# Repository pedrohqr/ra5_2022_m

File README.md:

# RA5 2022 M — Base Board (Raptor)

Base/carrier board for a modular PLC (Programmable Logic Controller): an I/O
front-end with no main MCU of its own — sensing and metering peripherals are
driven by a separate MCU+LTE modem card that plugs into the onboard M.2
Key-E socket (`J1`, visible in the photos below). The socket follows the M.2
mechanical form factor but uses a custom pinout (native 3.3V logic) — it is
not meant to accept an off-the-shelf M.2 card. The pluggable MCU+modem card
itself now lives in its own separate repository, developed independently
from this base board.

Main blocks on this board:

- **Power**: input via the `B0303S-1W` isolated DC-DC module, `TPS54202DDC`
  buck regulator, `AMS1117-3.3` linear regulator (USB rail), and a USB-C
  connector that passes through to `J1` for flashing/debugging the plugged-in
  MCU card.
- **2x differential 4-20mA analog inputs** via an `ADS1115` I2C ADC.
- **2x digital inputs and 2x digital outputs**, opto/divider-conditioned and
  transistor-driven respectively.
- **`ATM90E32AS` three-phase energy meter**, in a galvanically isolated
  domain (`GND2`/`VDD2`) from the rest of the board, bridged via the
  `ISO7741N1-Y` digital isolator (SPI) and a `CS817X20LS`-family isolator
  (power-mode select).
- **`STM8S003F3P` housekeeping MCU**, reading/driving the digital I/O signals
  and intended to expose them over the shared I2C bus on `J1`.
- `KF250-3.5-2P-2` screw terminals for the current loops and other
  field-side connections.

## Renders of the finished board

*Component-side view: the M.2 socket (`J1`) in the center, screw terminals
and field connectors along the edges, and the row of MOVs/varistors feeding
the energy-meter current inputs.*

*Same side, rotated ~180°, showing the USB-C connector, the STM8
housekeeping MCU, and the power section.*

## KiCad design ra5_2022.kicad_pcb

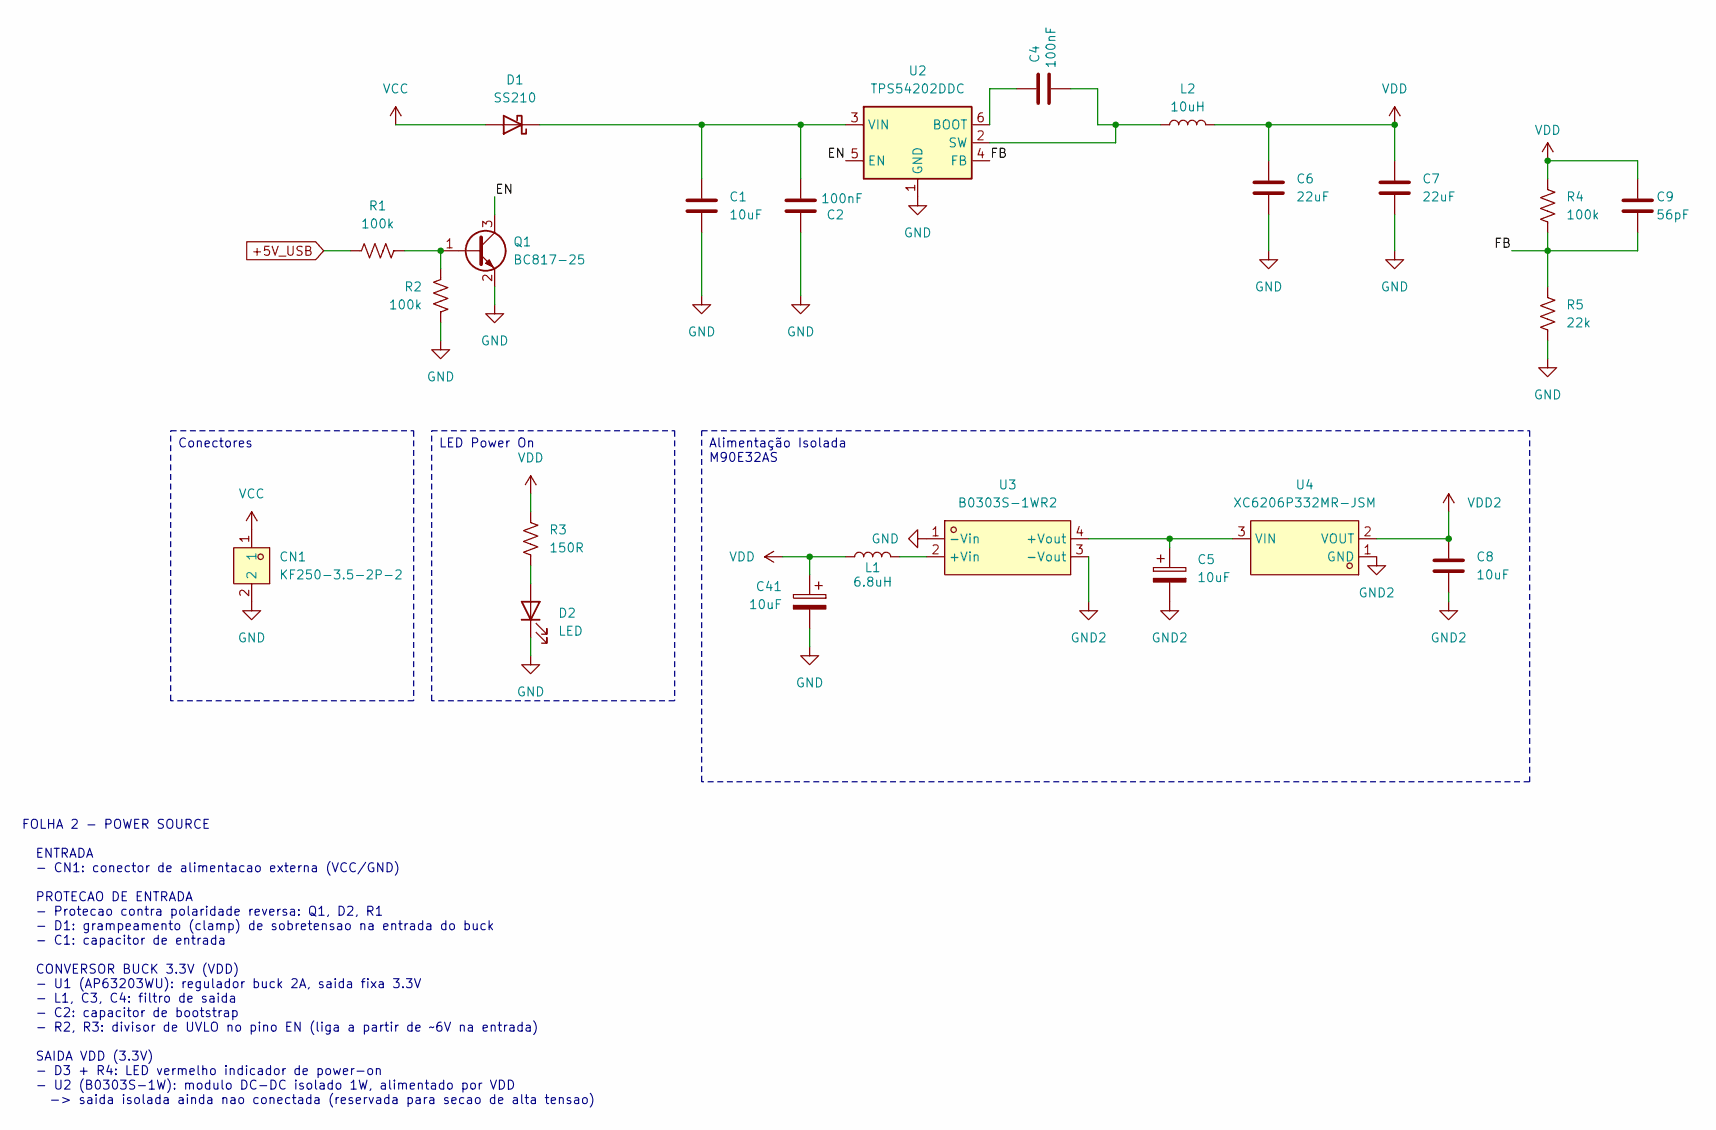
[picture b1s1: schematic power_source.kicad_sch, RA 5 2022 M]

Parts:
C1: 10uF; C_1206_3216Metric; MPN CL31A106KBHNNNE; JLCPCB Part # C13585
C2: 100nF; C_0402_1005Metric; MPN CL05B104KB54PNC; JLCPCB Part # C307331
C4: 100nF; C_0402_1005Metric; MPN CL05B104KO5NNNC; JLCPCB Part # C1525
C5, C41: 10uF; CP_Elec_4x5.4; MPN VT1E100M0405; JLCPCB Part # C22383768
C6, C7: 22uF; C_0603_1608Metric; MPN CL10A226MQ8NRNC; JLCPCB Part # C59461
C8: 10uF; C_0402_1005Metric; MPN CL05A106MQ5NUNC; JLCPCB Part # C15525
C9: 56pF; C_0603_1608Metric; MPN CL10C560JB8NNNC; JLCPCB Part # C39148
CN1: KF250-3.5-2P-2; CONN-TH_P3.50_KF250-3.5-2P-2; MPN KF250-3.5-2P-2; JLCPCB Part # C475163
D1: SS210; D_SMA; MPN SS210; JLCPCB Part # C14996
D2: LED; LED_0805_2012Metric; MPN YLED0805R; JLCPCB Part # C19171391
L1: 6.8uH; L_1008_2520Metric; MPN SLW252010S6R8MST; JLCPCB Part # C48533097
L2: 10uH; IND-SMD_L5.0-W5.0-1; MPN SLW5040S100MST; JLCPCB Part # C182189
Q1: BC817-25; SOT-23; MPN BC817-25; JLCPCB Part # C20069154
R1, R2, R4: 100k; R_0805_2012Metric; MPN 0805W8F1003T5E; JLCPCB Part # C149504
R3: 150R; R_0603_1608Metric; MPN 0603WAF1500T5E; JLCPCB Part # C22808
R5: 22k; R_0402_1005Metric; MPN 0402WGF2202TCE; JLCPCB Part # C25768
U2: TPS54202DDC; SOT-23-6; MPN TPS54202DDCR; JLCPCB Part # C191884
U3: B0303S-1WR2; PWRM-TH_BXXXXS-1WR2; MPN B0303S-1WR2; JLCPCB Part # C7598619
U4: XC6206P332MR-JSM; SOT-23-3_L3.0-W1.7-P0.95-LS2.9-BR; MPN XC6206P332MR-JSM; JLCPCB Part # C20616640

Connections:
+5V_USB: R1.1; also elsewhere on the board
/Power Source/EN: Q1.3 (C), U2.5 (EN)
/Power Source/FB: C9.2, R4.1, R5.1, U2.4 (FB)
GND: C1.2, C2.1, C6.2, C7.2, C41.2, CN1.2, D2.1 (K), Q1.2 (E), R2.1, R5.2, U2.1 (GND), U3.1 (-Vin); also elsewhere on the board
GND2: C5.2, C8.2, U3.3 (-Vout), U4.1 (GND); also elsewhere on the board
unnamed: C1.1, C2.2, D1.1 (K), U2.3 (VIN)
unnamed: D2.2 (A), R3.2
unnamed: Q1.1 (B), R1.2, R2.2
unnamed: C4.1, U2.6 (BOOT)
unnamed: C4.2, L2.1, U2.2 (SW)
unnamed: L1.2, U3.2 (+Vin)
unnamed: C5.1, U3.4 (+Vout), U4.3 (VIN)
VCC: CN1.1, D1.2 (A)
VDD: C6.1, C7.1, C9.1, C41.1, L1.1, L2.2, R3.1, R4.2; also elsewhere on the board
VDD2: C8.1, U4.2 (VOUT); also elsewhere on the board

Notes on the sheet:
FOLHA 2 - POWER SOURCE ENTRADA - CN1: conector de alimentacao externa (VCC/GND) PROTECAO DE ENTRADA - Protecao contra polaridade reversa: Q1, D2, R1 - D1: grampeamento (clamp) de sobretensao na entrada do buck - C1: capacitor de entrada CONVERSOR BUCK 3.3V (VDD) - U1 (AP63203WU): regulador buck 2A,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
Conectores
Alimentação Isolada M90E32AS
LED Power On

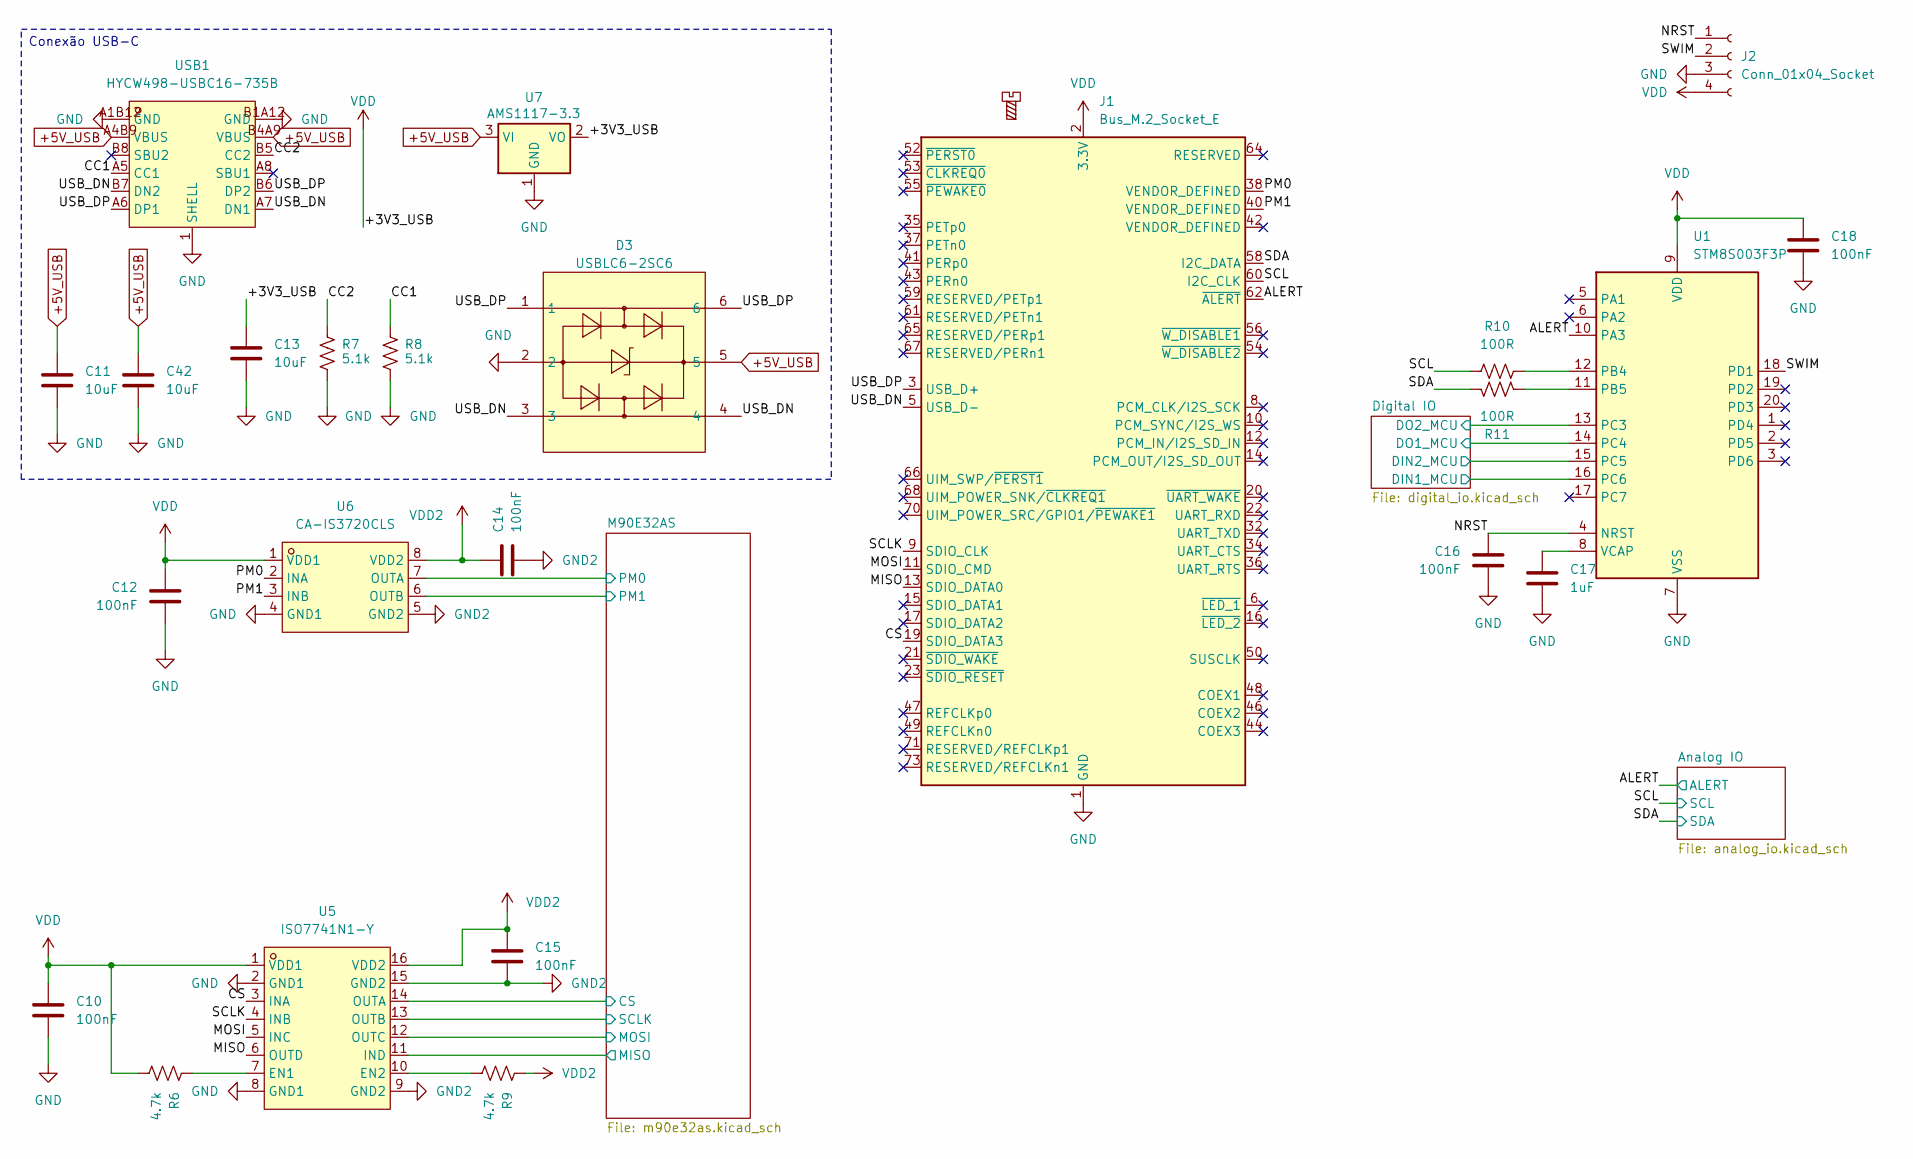
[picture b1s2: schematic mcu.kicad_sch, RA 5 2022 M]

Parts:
C10, C12, C14, C15, C16, C18: 100nF; C_0402_1005Metric; MPN CL05B104KO5NNNC; JLCPCB Part # C1525
C11, C13, C42: 10uF; C_0402_1005Metric; MPN CL05A106MQ5NUNC; JLCPCB Part # C15525
C17: 1uF; C_0402_1005Metric; MPN CL05A105KA5NQNC; JLCPCB Part # C52923
D3: USBLC6-2SC6; SOT-23-6_L2.9-W1.6-P0.95-LS2.8-BL; MPN USBLC6-2SC6; JLCPCB Part # C7519
H1: MountingScrew; MountingHole_2.2mm_M2_Pad_Via
J1: Bus_M.2_Socket_E; CONN-SMD_AS0BC21-S48BE-7H; MPN AS0BC21-S40BE-7H; JLCPCB Part # C410527
J2: Conn_01x04_Socket; PinHeader_1x04_P2.54mm_Vertical
R6, R9: 4.7k; R_0402_1005Metric; MPN 0402WGF4701TCE; JLCPCB Part # C25900
R7, R8: 5.1k; R_0603_1608Metric; MPN WR04X512JTL; JLCPCB Part # C384321
R10, R11: 100R; R_0402_1005Metric; MPN 0402WGF1000TCE; JLCPCB Part # C25076
U1: STM8S003F3P; TSSOP-20_4.4x6.5mm_P0.65mm; MPN STM8S003F3P6TR; JLCPCB Part # C52717
U5: ISO7741N1-Y; SOIC-16_L9.9-W3.9-P1.27-LS6.0-BL-1; MPN ISO7741N1-Y; JLCPCB Part # C53446593
U6: CA-IS3720CLS; SOIC-8_L4.9-W3.9-P1.27-LS6.0-BL; MPN CA-IS3720CLS; JLCPCB Part # C41784134
U7: AMS1117-3.3; SOT-223-3_TabPin2; MPN AMS1117-3.3OF; JLCPCB Part # C50313802
USB1: HYCW498-USBC16-735B; USB-C-SMD_HYCW498-USBC16-735B; MPN HYCW498-USBC16-735B; JLCPCB Part # C42400252

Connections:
+5V_USB: C11.1, C42.1, D3.5, U7.3 (VI), USB1.A4B9 (VBUS), USB1.B4A9 (VBUS); also elsewhere on the board
/MCU/ALERT: J1.62 (~ALERT), U1.10 (PA3); also elsewhere on the board
/MCU/CC1: R8.2, USB1.A5 (CC1)
/MCU/CC2: R7.2, USB1.B5 (CC2)
/MCU/CS: J1.19 (SDIO_DATA3), U5.3 (INA)
/MCU/Digital IO/DIN1_MCU: U1.16 (PC6); also elsewhere on the board
/MCU/Digital IO/DIN2_MCU: U1.15 (PC5); also elsewhere on the board
/MCU/Digital IO/DO1_MCU: U1.14 (PC4); also elsewhere on the board
/MCU/Digital IO/DO2_MCU: U1.13 (PC3); also elsewhere on the board
/MCU/M90E32AS/CS: U5.14 (OUTA); also elsewhere on the board
/MCU/M90E32AS/MISO: U5.11 (IND); also elsewhere on the board
/MCU/M90E32AS/MOSI: U5.12 (OUTC); also elsewhere on the board
/MCU/M90E32AS/PM0: U6.7 (OUTA); also elsewhere on the board
/MCU/M90E32AS/PM1: U6.6 (OUTB); also elsewhere on the board
/MCU/M90E32AS/SCLK: U5.13 (OUTB); also elsewhere on the board
/MCU/MISO: J1.13 (SDIO_DATA0), U5.6 (OUTD)
/MCU/MOSI: J1.11 (SDIO_CMD), U5.5 (INC)
/MCU/NRST: C16.1, J2.1, U1.4 (NRST)
/MCU/PM0: J1.38 (VENDOR_DEFINED), U6.2 (INA)
/MCU/PM1: J1.40 (VENDOR_DEFINED), U6.3 (INB)
/MCU/SCL: J1.60 (I2C_CLK), R10.1; also elsewhere on the board
/MCU/SCLK: J1.9 (SDIO_CLK), U5.4 (INB)
/MCU/SDA: J1.58 (I2C_DATA), R11.1; also elsewhere on the board
/MCU/SWIM: J2.2, U1.18 (PD1)
GND: C10.2, C11.2, C12.2, C13.2, C16.2, C17.2, C18.2, C42.2, D3.2, J1.1 (GND), J1.7 (GND), J1.18 (GND), J1.33 (GND), J1.39 (GND), J1.45 (GND), J1.51 (GND), J1.57 (GND), J1.63 (GND), J1.69 (GND), J1.75 (GND), J2.3, R7.1, R8.1, U1.7 (VSS), U5.2 (GND1), U5.8 (GND1), U6.4 (GND1), U7.1 (GND), USB1.1 (SHELL), USB1.A1B12 (GND), USB1.B1A12 (GND); also elsewhere on the board
GND2: C14.2, C15.2, U5.9 (GND2), U5.15 (GND2), U6.5 (GND2); also elsewhere on the board
unnamed: R10.2, U1.12 (PB4)
unnamed: R11.2, U1.11 (PB5)
unnamed: C17.1, U1.8 (VCAP)
unnamed: R6.2, U5.7 (EN1)
unnamed: R9.1, U5.10 (EN2)
VDD: C10.1, C12.1, C13.1, C18.1, J1.2 (3.3V), J1.4 (3.3V), J1.72 (3.3V), J1.74 (3.3V), J2.4, R6.1, U1.9 (VDD), U5.1 (VDD1), U6.1 (VDD1), U7.2 (VO); also elsewhere on the board
VDD2: C14.1, C15.1, R9.2, U5.16 (VDD2), U6.8 (VDD2); also elsewhere on the board

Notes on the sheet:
Conexão USB-C

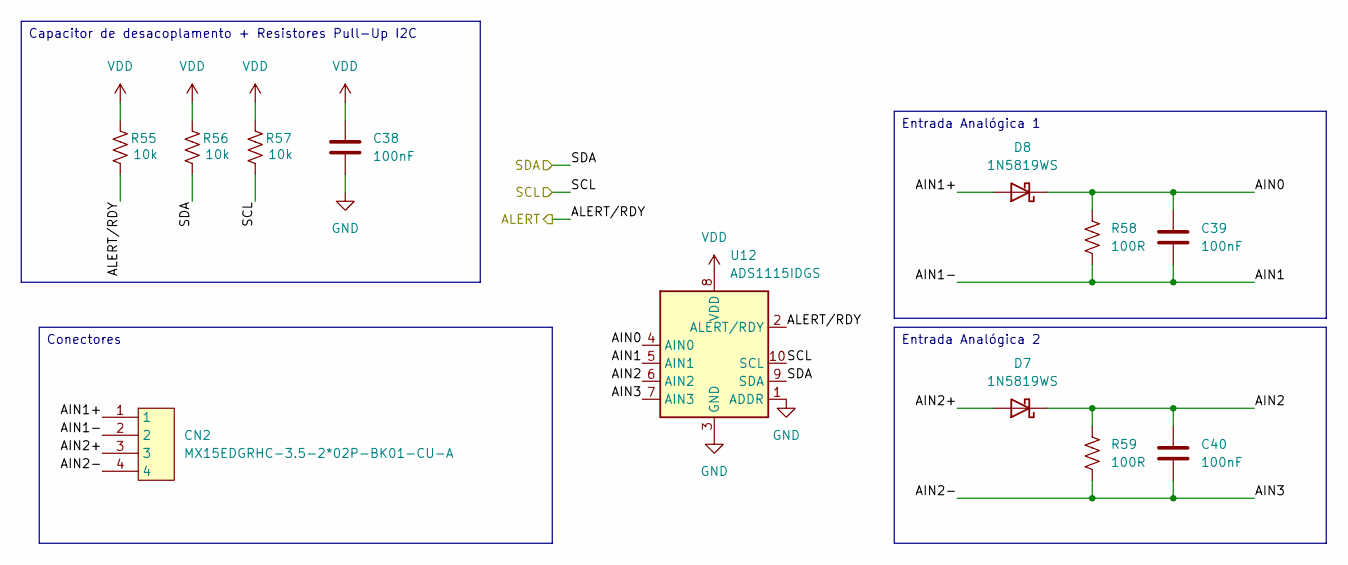
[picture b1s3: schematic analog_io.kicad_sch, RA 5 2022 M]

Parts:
C38, C39, C40: 100nF; C_0402_1005Metric; MPN CL05B104KO5NNNC; JLCPCB Part # C1525
CN2: MX15EDGRHC-3.5-2*02P-BK01-CU-A; CONN-TH_4P-P3.50_JL15EDGRHC-35002B01; MPN MX15EDGRHC-3.5-2*02P-BK01-Cu-A; JLCPCB Part # C49142488
D7, D8: 1N5819WS; D_SOD-323; MPN 1N5819WS; JLCPCB Part # C191023
R55, R56, R57: 10k; R_0402_1005Metric; MPN 0402WGF1002TCE; JLCPCB Part # C25744
R58, R59: 100R; R_1206_3216Metric; MPN 1206W4F1000T5E; JLCPCB Part # C17901
U12: ADS1115IDGS; TSSOP-10_3x3mm_P0.5mm; MPN ADS1115IDGSR; JLCPCB Part # C37593

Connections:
/MCU/ALERT: R55.1, U12.2 (ALERT/RDY); also elsewhere on the board
/MCU/Analog IO/AIN0: C39.1, D8.1 (K), R58.1, U12.4 (AIN0)
/MCU/Analog IO/AIN1: C39.2, CN2.2, R58.2, U12.5 (AIN1)
/MCU/Analog IO/AIN1+: CN2.1, D8.2 (A)
/MCU/Analog IO/AIN2: C40.1, D7.1 (K), R59.1, U12.6 (AIN2)
/MCU/Analog IO/AIN2+: CN2.3, D7.2 (A)
/MCU/Analog IO/AIN2-: C40.2, CN2.4, R59.2, U12.7 (AIN3)
/MCU/SCL: R57.1, U12.10 (SCL); also elsewhere on the board
/MCU/SDA: R56.1, U12.9 (SDA); also elsewhere on the board
GND: C38.2, U12.1 (ADDR), U12.3 (GND); also elsewhere on the board
VDD: C38.1, R55.2, R56.2, R57.2, U12.8 (VDD); also elsewhere on the board

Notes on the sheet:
Capacitor de desacoplamento + Resistores Pull-Up I2C
Conectores
Entrada Analógica 2
Entrada Analógica 1

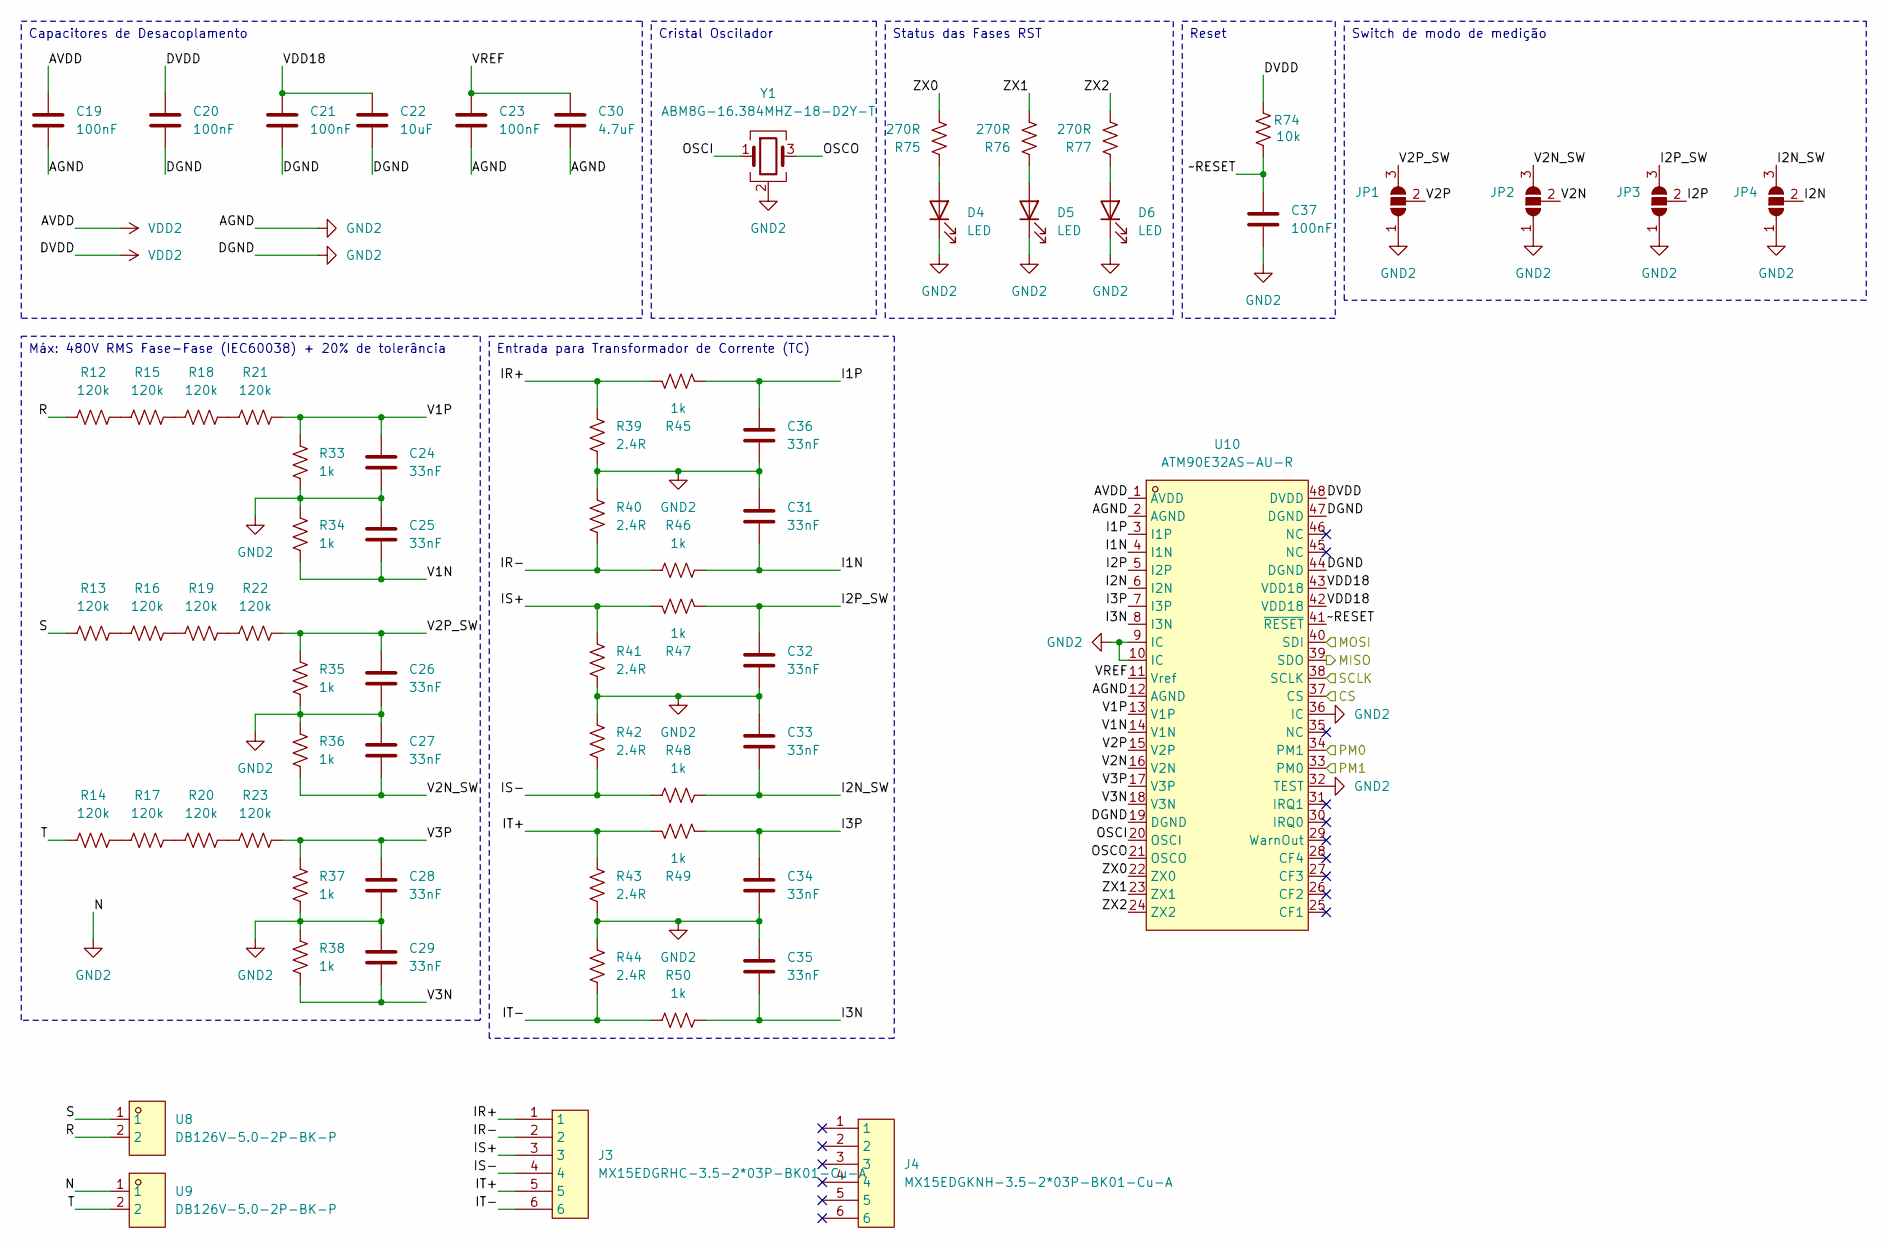
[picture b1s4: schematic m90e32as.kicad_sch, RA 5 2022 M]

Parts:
C19, C20, C21, C23, C37: 100nF; C_0402_1005Metric; MPN CL05B104KO5NNNC; JLCPCB Part # C1525
C22: 10uF; C_0402_1005Metric; MPN CL05A106MQ5NUNC; JLCPCB Part # C15525
C24, C25, C26, C27, C28, C29, C31, C32, C33, C34, C35, C36: 33nF; C_0805_2012Metric; MPN 0805B333K500NT; JLCPCB Part # C1739
C30: 4.7uF; C_0402_1005Metric; MPN CL05A475MP5NRNC; JLCPCB Part # C23733
D4, D5, D6: LED; LED_0603_1608Metric; MPN 19-219/GHC-YR2T1B5Y/3T; JLCPCB Part # C2994781
J3: MX15EDGRHC-3.5-2*03P-BK01-Cu-A; MX15EDGRHC-3.5-2x03P; MPN MX15EDGRHC-3.5-2*03P-BK01-Cu-A; JLCPCB Part # C49142489
J4: MX15EDGKNH-3.5-2*03P-BK01-Cu-A; MPN MX15EDGKNH-3.5-2*03P-BK01-Cu-A; JLCPCB Part # C49142469
JP1, JP2, JP3, JP4: SolderJumper_3_Open; SolderJumper-3_P1.3mm_Open_RoundedPad1.0x1.5mm_NumberLabels
R12, R13, R14, R15, R16, R17, R18, R19, R20, R21, R22, R23: 120k; R_Axial_DIN0207_L6.3mm_D2.5mm_P10.16mm_Horizontal; MPN MF1/4W-120KΩ±1% T; JLCPCB Part # C119370
R33, R34, R35, R36, R37, R38, R45, R46, R47, R48, R49, R50: 1k; R_0402_1005Metric; MPN 0402WGF1001TCE; JLCPCB Part # C11702
R39, R40, R41, R42, R43, R44: 2.4R; R_0603_1608Metric; MPN FRC0603F2R40TS; JLCPCB Part # C2998116
R74: 10k; R_0402_1005Metric; MPN 0402WGF1002TCE; JLCPCB Part # C25744
R75, R76, R77: 270R; R_0603_1608Metric; MPN 0603WAF2700T5E; JLCPCB Part # C22966
U8, U9: DB126V-5.0-2P-BK-P; CONN-TH_2P-P5.00_DIBO_DB126V-5.0-2P-BU-P; MPN DB126V-5.0-2P-BK-P; JLCPCB Part # C49260677
U10: ATM90E32AS-AU-R; TQFP-48_L7.0-W7.0-P0.50-LS9.0-BL; MPN ATM90E32AS-AU-R; JLCPCB Part # C177153
Y1: ABM8G-16.384MHZ-18-D2Y-T; Crystal_SMD_3225-4Pin_3.2x2.5mm; MPN ABM8G-16.384MHZ-18-D2Y-T; JLCPCB Part # C7065080

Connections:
/MCU/M90E32AS/CS: U10.37 (CS); also elsewhere on the board
/MCU/M90E32AS/I1N: C31.2, R46.2, U10.4 (I1N)
/MCU/M90E32AS/I1P: C36.1, R45.2, U10.3 (I1P)
/MCU/M90E32AS/I2N: JP4.2 (C), U10.6 (I2N)
/MCU/M90E32AS/I2N_SW: C33.2, JP4.3 (B), R48.2
/MCU/M90E32AS/I2P: JP3.2 (C), U10.5 (I2P)
/MCU/M90E32AS/I2P_SW: C32.1, JP3.3 (B), R47.2
/MCU/M90E32AS/I3N: C35.2, R50.2, U10.8 (I3N)
/MCU/M90E32AS/I3P: C34.1, R49.2, U10.7 (I3P)
/MCU/M90E32AS/IR+: J3.1, R39.1, R45.1
/MCU/M90E32AS/IR-: J3.2, R40.2, R46.1
/MCU/M90E32AS/IS+: J3.3, R41.1, R47.1
/MCU/M90E32AS/IS-: J3.4, R42.2, R48.1
/MCU/M90E32AS/IT+: J3.5, R43.1, R49.1
/MCU/M90E32AS/IT-: J3.6, R44.2, R50.1
/MCU/M90E32AS/MISO: U10.39 (SDO); also elsewhere on the board
/MCU/M90E32AS/MOSI: U10.40 (SDI); also elsewhere on the board
/MCU/M90E32AS/OSCI: U10.20 (OSCI), Y1.1
/MCU/M90E32AS/OSCO: U10.21 (OSCO), Y1.3
/MCU/M90E32AS/PM0: U10.34 (PM1); also elsewhere on the board
/MCU/M90E32AS/PM1: U10.33 (PM0); also elsewhere on the board
/MCU/M90E32AS/R: R12.1, U8.2
/MCU/M90E32AS/S: R13.1, U8.1
/MCU/M90E32AS/SCLK: U10.38 (SCLK); also elsewhere on the board
/MCU/M90E32AS/T: R14.1, U9.2
/MCU/M90E32AS/V1N: C25.2, R34.2, U10.14 (V1N)
/MCU/M90E32AS/V1P: C24.1, R21.2, R33.1, U10.13 (V1P)
/MCU/M90E32AS/V2N: JP2.2 (C), U10.16 (V2N)
/MCU/M90E32AS/V2N_SW: C27.2, JP2.3 (B), R36.2
/MCU/M90E32AS/V2P: JP1.2 (C), U10.15 (V2P)
/MCU/M90E32AS/V2P_SW: C26.1, JP1.3 (B), R22.2, R35.1
/MCU/M90E32AS/V3N: C29.2, R38.2, U10.18 (V3N)
/MCU/M90E32AS/V3P: C28.1, R23.2, R37.1, U10.17 (V3P)
/MCU/M90E32AS/VDD18: C21.1, C22.1, U10.42 (VDD18), U10.43 (VDD18)
/MCU/M90E32AS/VREF: C23.1, C30.1, U10.11 (Vref)
/MCU/M90E32AS/ZX0: R75.1, U10.22 (ZX0)
/MCU/M90E32AS/ZX1: R76.1, U10.23 (ZX1)
/MCU/M90E32AS/ZX2: R77.1, U10.24 (ZX2)
/MCU/M90E32AS/~RESET: C37.1, R74.1, U10.41 (~RESET)
GND2: C19.2, C20.2, C21.2, C22.2, C23.2, C24.2, C25.1, C26.2, C27.1, C28.2, C29.1, C30.2, C31.1, C32.2, C33.1, C34.2, C35.1, C36.2, C37.2, D4.1 (K), D5.1 (K), D6.1 (K), JP1.1 (A), JP2.1 (A), JP3.1 (A), JP4.1 (A), R33.2, R34.1, R35.2, R36.1, R37.2, R38.1, R39.2, R40.1, R41.2, R42.1, R43.2, R44.1, U9.1, U10.2 (AGND), U10.9 (IC), U10.10 (IC), U10.12 (AGND), U10.19 (DGND), U10.32 (TEST), U10.36 (IC), U10.44 (DGND), U10.47 (DGND), Y1.2 (G), Y1.4 (G); also elsewhere on the board
unnamed: D4.2 (A), R75.2
unnamed: D5.2 (A), R76.2
unnamed: D6.2 (A), R77.2
unnamed: R12.2, R15.1
unnamed: R13.2, R16.1
unnamed: R14.2, R17.1
unnamed: R15.2, R18.1
unnamed: R16.2, R19.1
unnamed: R17.2, R20.1
unnamed: R18.2, R21.1
unnamed: R19.2, R22.1
unnamed: R20.2, R23.1
VDD2: C19.1, C20.1, R74.2, U10.1 (AVDD), U10.48 (DVDD); also elsewhere on the board

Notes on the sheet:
Capacitores de Desacoplamento
Cristal Oscilador
Reset
Entrada para Transformador de Corrente (TC)
Máx: 480V RMS Fase-Fase (IEC60038) + 20% de tolerância
Status das Fases RST
Switch de modo de medição

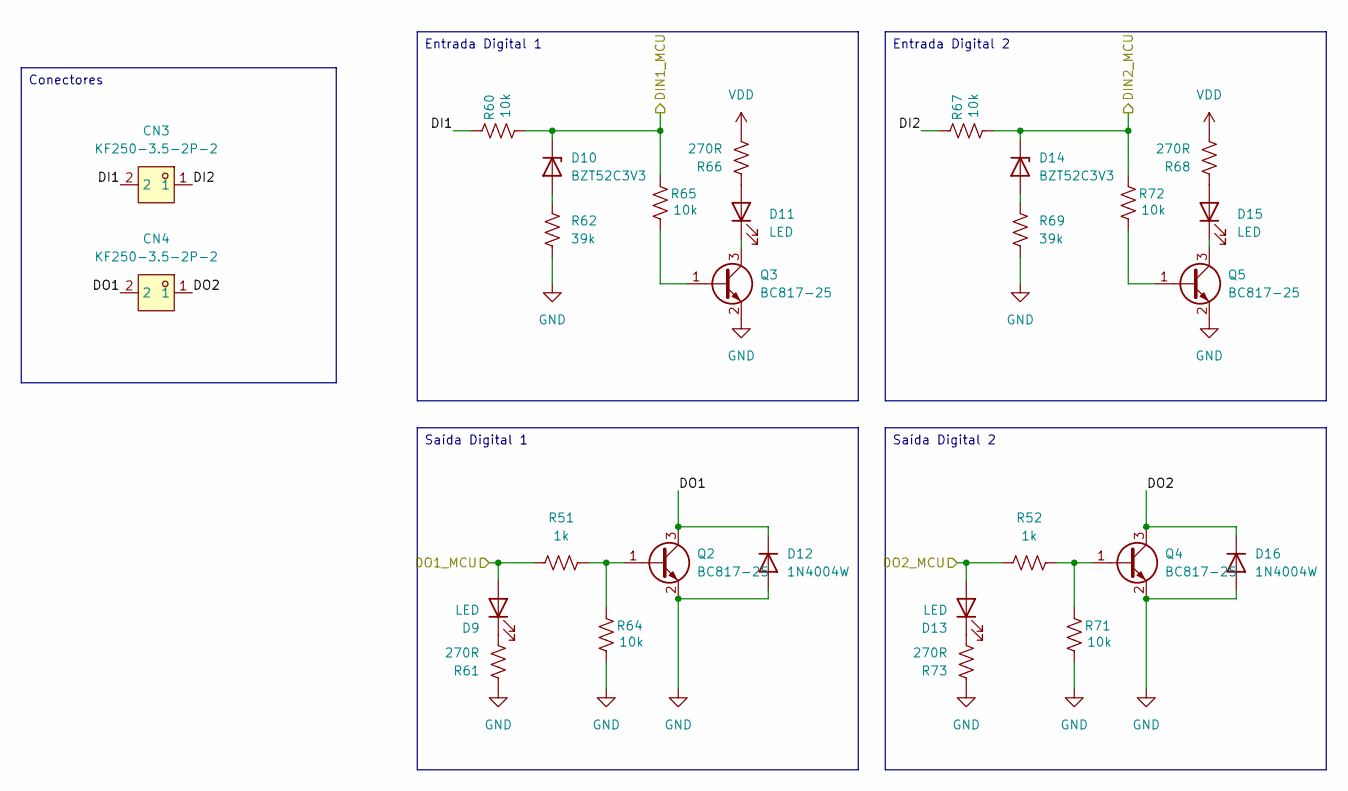
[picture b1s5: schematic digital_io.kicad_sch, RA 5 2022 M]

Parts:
CN3, CN4: KF250-3.5-2P-2; CONN-TH_P3.50_KF250-3.5-2P-2; MPN KF250-3.5-2P-2; JLCPCB Part # C475163
D9, D11, D13, D15: LED; LED_0805_2012Metric; MPN YLED0805R; JLCPCB Part # C19171391
D10, D14: BZT52C3V3; D_SOD-123; MPN BZT52C3V3; JLCPCB Part # C216707
D12, D16: 1N4004W; D_SOD-123F; MPN 1N4004W; JLCPCB Part # C162734
Q2, Q3, Q4, Q5: BC817-25; SOT-23; MPN BC817-25; JLCPCB Part # C20069154
R51, R52: 1k; R_0402_1005Metric; MPN 0402WGF1001TCE; JLCPCB Part # C11702
R60, R64, R65, R67, R71, R72: 10k; R_0402_1005Metric; MPN 0402WGF1002TCE; JLCPCB Part # C25744
R61, R66, R68, R73: 270R; R_0603_1608Metric; MPN 0603WAF2700T5E; JLCPCB Part # C22966
R62, R69: 39k; R_0603_1608Metric; MPN 0603WAF3902T5E; JLCPCB Part # C23153

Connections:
/MCU/Digital IO/DI1: CN3.2, R60.2
/MCU/Digital IO/DI2: CN3.1, R67.2
/MCU/Digital IO/DIN1_MCU: D10.1 (K), R60.1, R65.2; also elsewhere on the board
/MCU/Digital IO/DIN2_MCU: D14.1 (K), R67.1, R72.2; also elsewhere on the board
/MCU/Digital IO/DO1: CN4.2, D12.1 (K), Q2.3 (C)
/MCU/Digital IO/DO1_MCU: D9.2 (A), R51.1; also elsewhere on the board
/MCU/Digital IO/DO2: CN4.1, D16.1 (K), Q4.3 (C)
/MCU/Digital IO/DO2_MCU: D13.2 (A), R52.1; also elsewhere on the board
GND: D12.2 (A), D16.2 (A), Q2.2 (E), Q3.2 (E), Q4.2 (E), Q5.2 (E), R61.2, R62.1, R64.1, R69.1, R71.1, R73.2; also elsewhere on the board
unnamed: D9.1 (K), R61.1
unnamed: D10.2 (A), R62.2
unnamed: D11.2 (A), R66.2
unnamed: D11.1 (K), Q3.3 (C)
unnamed: D13.1 (K), R73.1
unnamed: D14.2 (A), R69.2
unnamed: D15.2 (A), R68.2
unnamed: D15.1 (K), Q5.3 (C)
unnamed: Q2.1 (B), R51.2, R64.2
unnamed: Q3.1 (B), R65.1
unnamed: Q4.1 (B), R52.2, R71.2
unnamed: Q5.1 (B), R72.1
VDD: R66.1, R68.1; also elsewhere on the board

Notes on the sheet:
Saída Digital 1
Entrada Digital 2
Saída Digital 2
Conectores
Entrada Digital 1

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
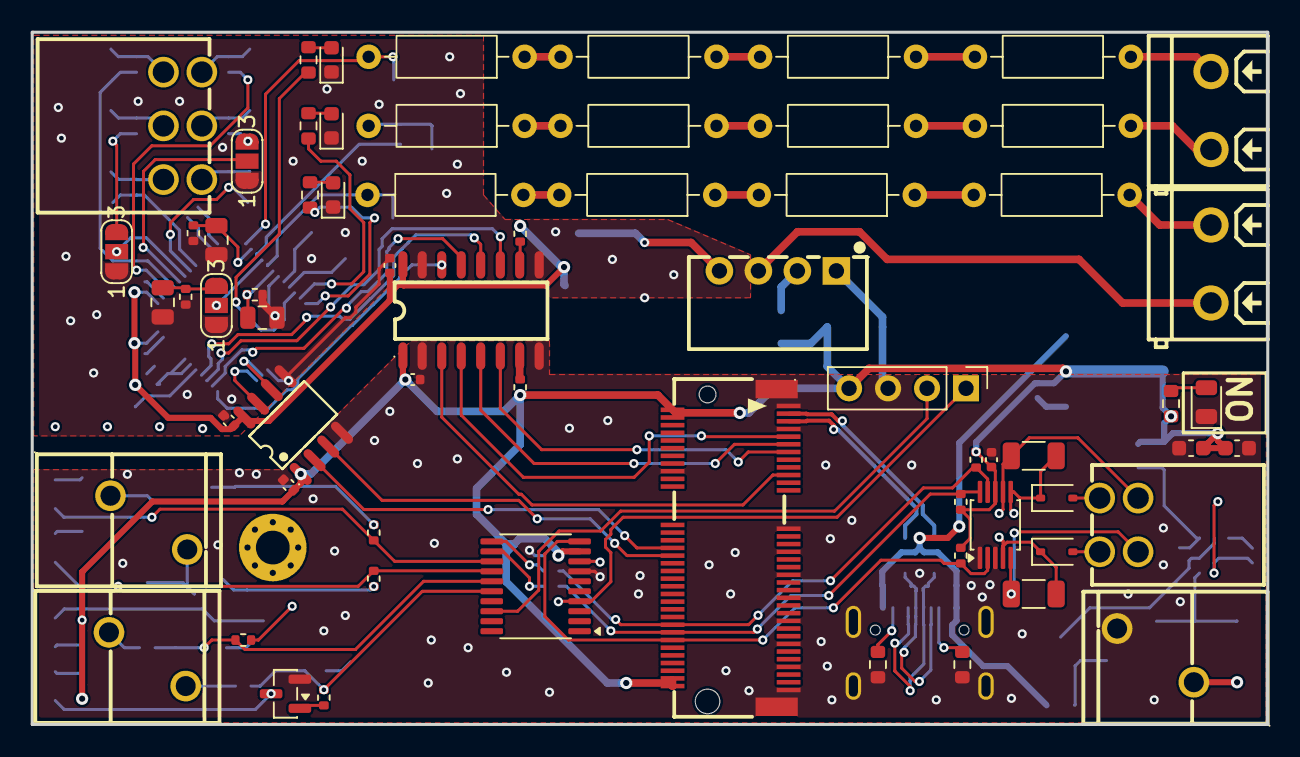
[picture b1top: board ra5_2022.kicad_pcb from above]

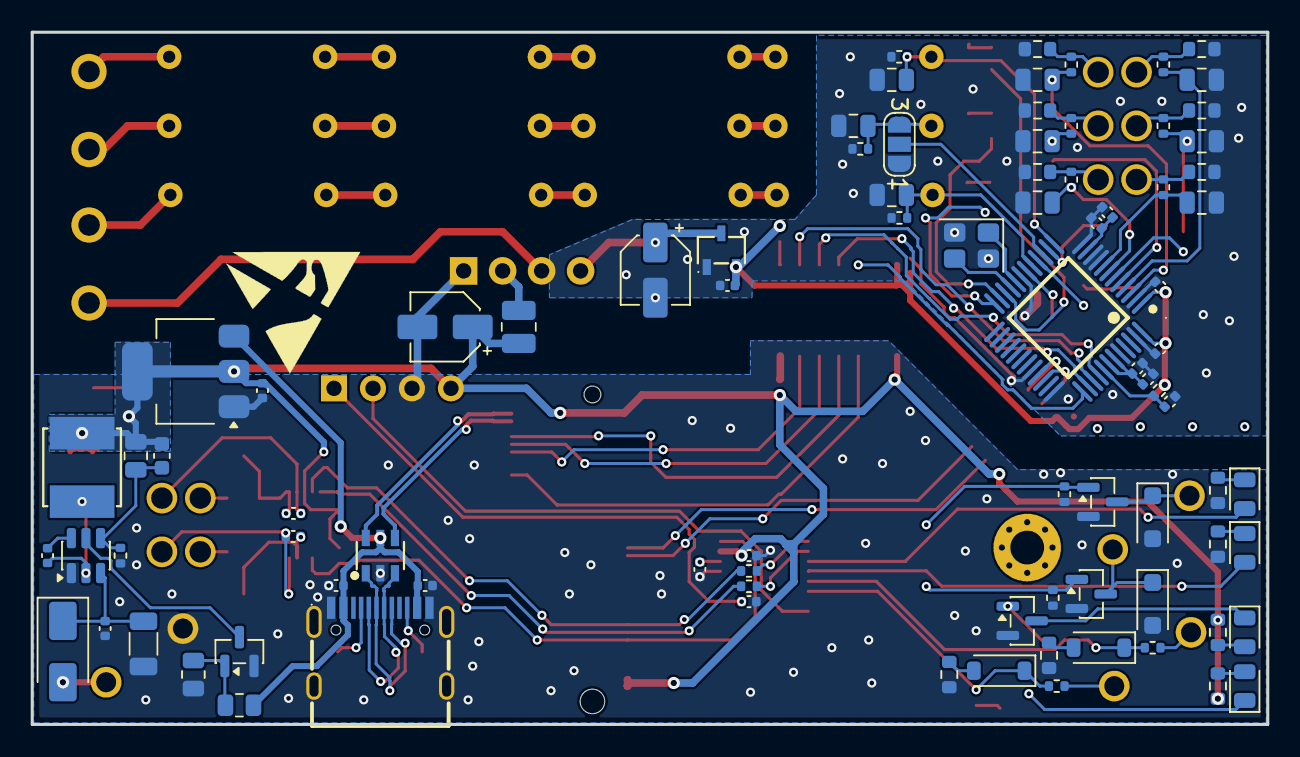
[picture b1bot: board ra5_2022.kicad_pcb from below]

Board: 2 copper layers, 80.5 x 45.1 mm, 153 parts (86 on the bottom side), 114 nets.
